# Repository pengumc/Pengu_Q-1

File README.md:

Pengu_Q-1
=========

Q1 quadruped robot control software

usage:
------
 - build the quadruped library under /quadruped
 - run qpview.py from within /hmatrix_visualizer (you may need to help your os with finding the quadruped library)

media:
------
www.youtube.com/watch?v=90h8AxxW2I0

http://pengurobotics.com/projects/Q1

http://hackaday.io/project/3229-pengu-q1-quadruped

3D printer files
----------------
http://www.thingiverse.com/thing:161885

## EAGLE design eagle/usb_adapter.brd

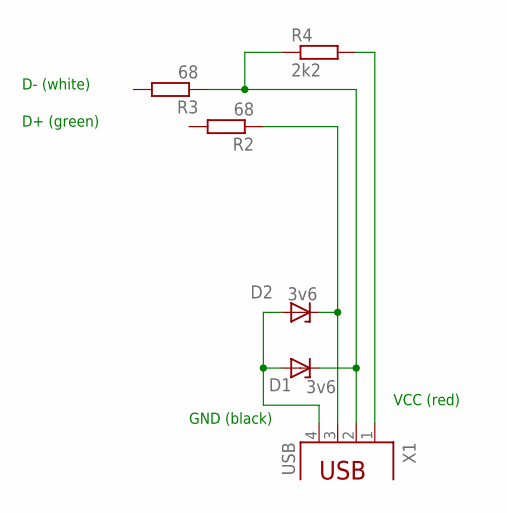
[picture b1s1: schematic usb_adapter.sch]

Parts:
D1, D2: 3v6; DO34Z7
R2, R3: 68; 0204/7
R4: 2k2; 0204/7
X1: USB; PN61729

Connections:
DMIN: D1.C, R3.1, R4.1, X1.2
DPLUS: D2.C, R2.1, X1.3
GND: D1.A, D2.A, X1.4
unnamed: R4.2, X1.1

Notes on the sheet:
D- (white)
D+ (green)
GND (black)
VCC (red)

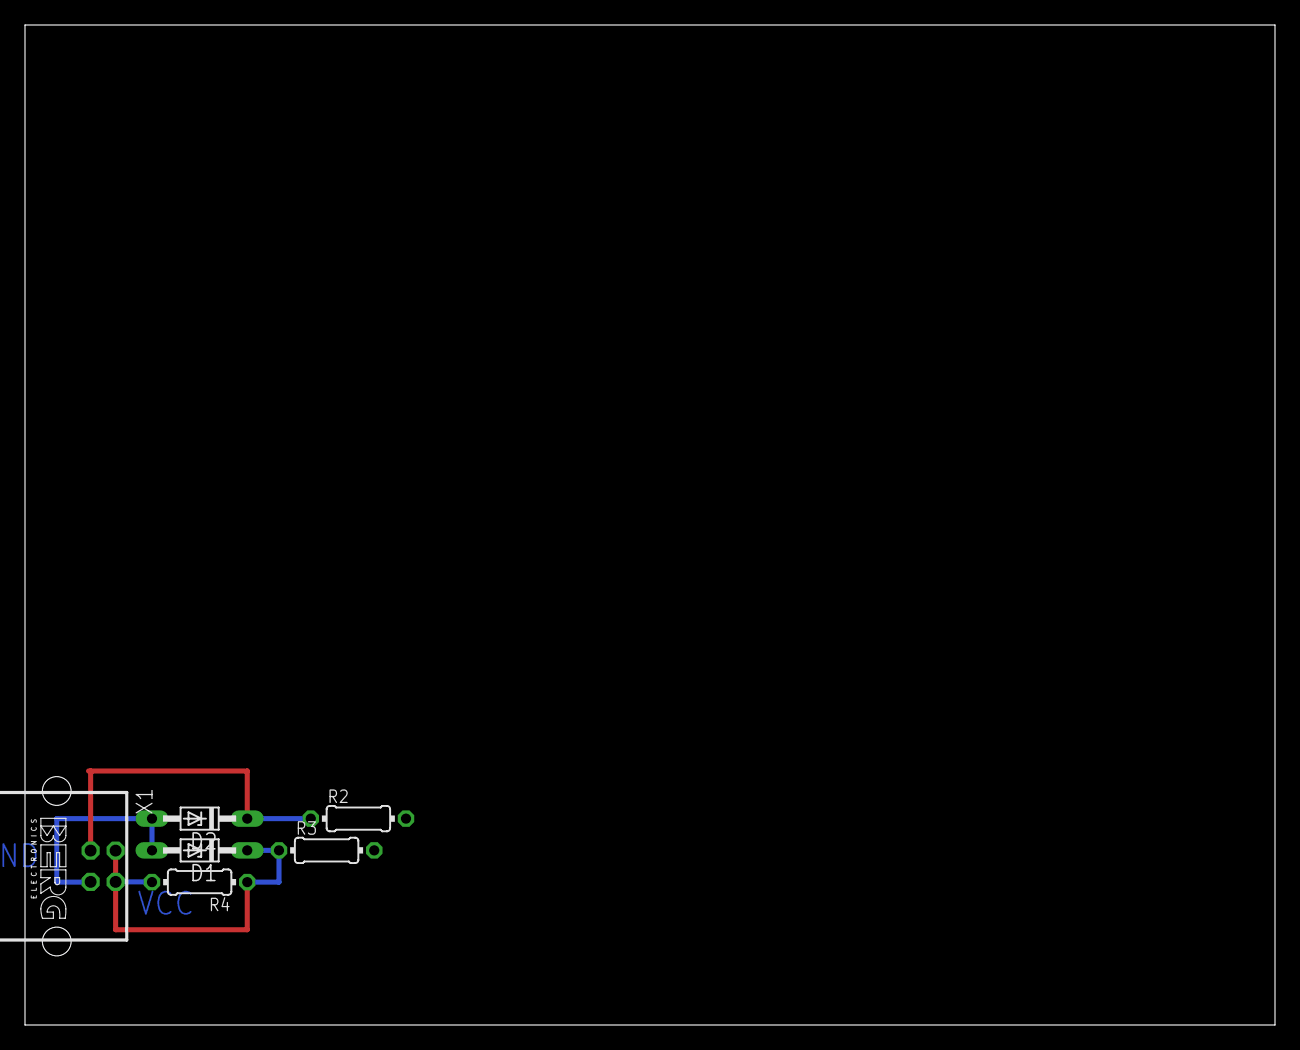
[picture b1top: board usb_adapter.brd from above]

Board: 2 copper layers, 100.0 x 80.0 mm, 6 parts (0 on the bottom side), 4 nets.

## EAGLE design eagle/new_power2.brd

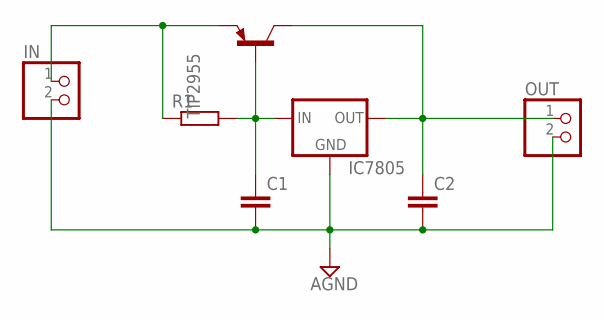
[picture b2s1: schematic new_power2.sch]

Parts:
C1, C2: C-EU025-024X044; C025-024X044
IC7805: 78XXL
IN: PINHD-1X2; 1X02
OUT: PINHD-1X2; 1X02
R1: R-EU_0204/5; 0204/5
TIP2955: -PNP-TO220; TO220

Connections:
AGND: C1.2, C2.2, IC7805.GND, IN.2, OUT.2
unnamed: IN.1, R1.1, TIP2955.3 (E)
unnamed: C1.1, IC7805.IN, R1.2, TIP2955.1 (B)
unnamed: C2.1, IC7805.OUT, OUT.1, TIP2955.2 (C)

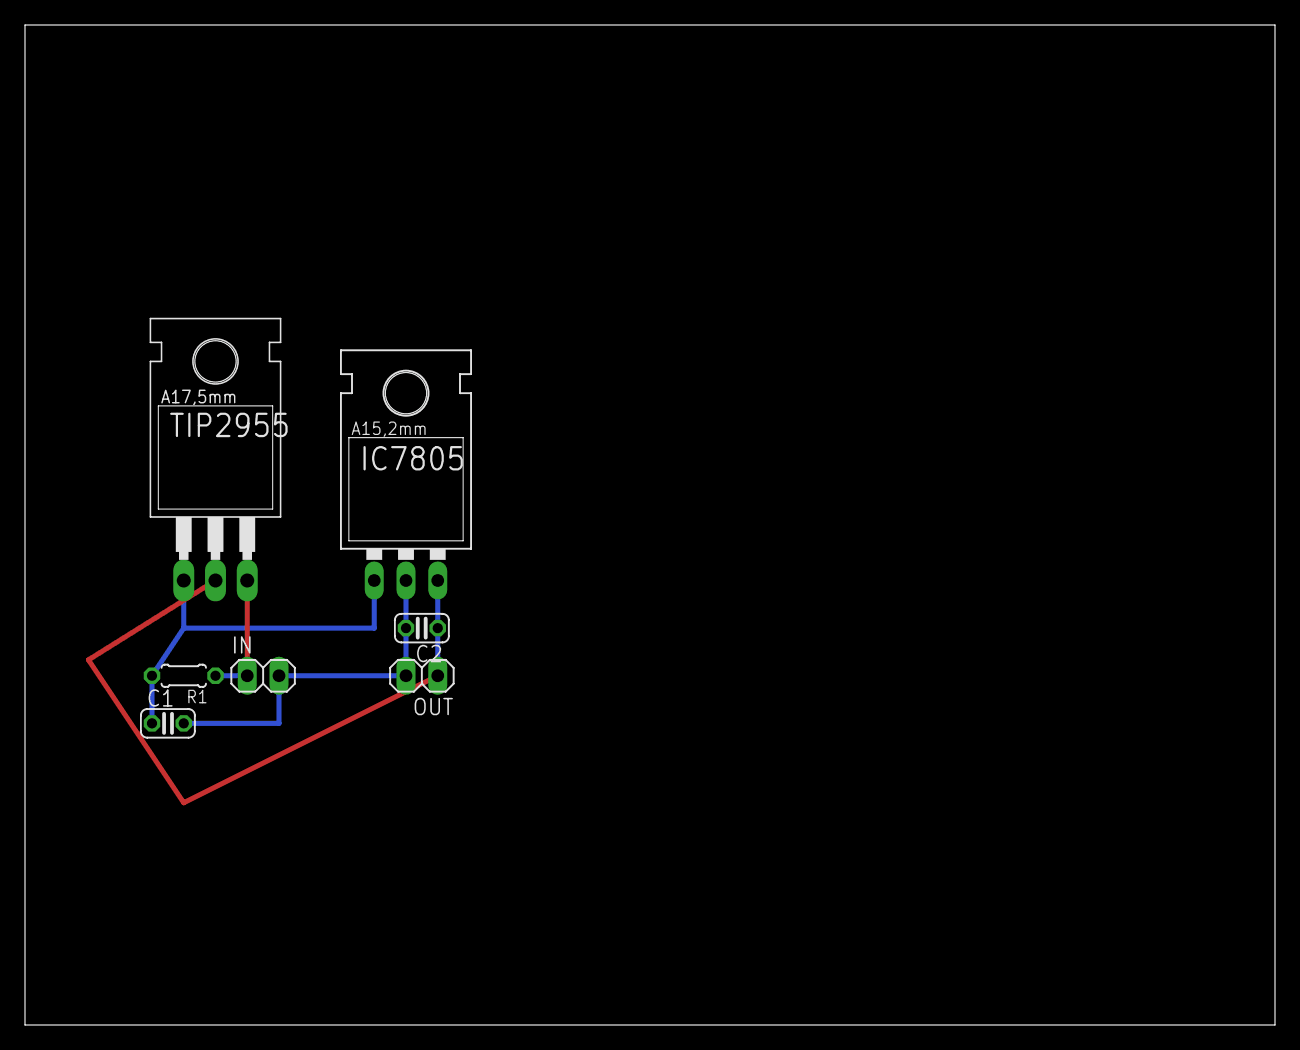
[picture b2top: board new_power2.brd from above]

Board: 2 copper layers, 100.0 x 80.0 mm, 7 parts (0 on the bottom side), 4 nets.

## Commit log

2013-11-02 start
2013-11-03 rudimentary screen
2013-11-16 messing around
2013-11-16 quit event
2013-12-31 add tested files
2013-12-31 added q1webgl files
2013-12-31 cleanup
    webgl enabled
2014-01-18 3d position sync, hover+az
2014-01-18 a/z for legs and body
2014-03-21 more classes
2014-03-21 visualization mockup
2014-03-22 unfinished pivot
2014-03-24 code fixes, added linux support
2014-03-24 added utility, fixed makefile for linux
2014-03-24 pivot done
2014-03-24 doc update
2014-03-27 stash
2014-04-26 HMatrix exposed
2014-05-08 python version of getch
2014-05-08 style fix
2014-05-08 simple start
2014-05-08 new HMatrix constructor
2014-05-08 wrapper groundwork done
2014-05-08 trying for an updating pyplot
2014-05-08 SelfDot
2014-05-08 doc update + threaded plot
2014-05-08 configure pivot orientation
2014-05-09 linux threaded ctypes workaround
2014-05-09 transform tree
2014-05-09 hardcoded config
2014-05-09 xml based config
2014-05-12 added offset to pivot, axis_ is removed in favor of config by R
2014-05-12 change angle
2014-05-12 better doc update
2014-05-12 no pdfs
2014-05-12 start IK dev
2014-05-12 math
2014-05-13 succes with a single pivot
2014-05-13 2 pivot test
2014-05-13 IK testing
2014-05-13 3 pivots hardcoded with view
2014-05-14 IK working
2014-05-14 more doc
2014-05-26 start usbcom dev with hidapi
    libraries in bin are for 64 bit linux and windows (32 and 64 bit)
2014-05-26 fixes for makefile, minor other changes
2014-05-28 sync functions
2014-05-28 up down testing
2014-07-26 schematic fix + usb adapter
2014-07-27 CoM compiles, time for testing
2014-07-27 CoM bugfix, wrapper
2014-08-03 COM added + recalibrate
2014-08-03 documentation update
2014-08-03 first steps
2014-08-09 calibration bios
2014-08-10 at least it compiles now
2014-08-10 exposed gaitgenerator configuration
2014-08-11 added gaitgenerator velocity, fixed HL
2014-08-22 removed doc from repo
2014-08-22 config fix
2014-08-22 testing...
2014-08-24 added gaitgenerator step
2014-08-24 animated plots!
2014-08-24 topdown view
2014-08-25 gaitgenerator working
2014-09-12 added L_min in gaitgenerator
2014-09-12 moving towards support for new servocontroller
2014-09-13 broken. WriteServoPulsewidths works
2014-09-13 still broken, read works
2014-09-13 new servocontroller works
2014-09-14 meaning of offset changed. recalibrated
2014-09-19 config update, circle motion
2014-09-19 new class SpringGG
2014-09-19 forces are correct
2014-09-20 pattern check
2014-09-20 removed rogg gaitgenerator
2014-09-20 quadruped.cpp formatting
2014-09-20 basic functionality is there
2014-09-20 working demo
2014-09-21 quick mashup of temporary power board
2014-10-11 added equalize feet levels function
2014-10-11 updated makefile
2014-10-11 body rotation
2014-10-26 added controller support, renamed rotation functions
2014-10-26 inverse kinematics demo stuff
2014-11-04 simple body circle
2014-12-11 removed cpplint from github
2014-12-16 diagonal vector finding
2014-12-21 move to support pattern
2014-12-22 temporary rest vector
2014-12-22 stylecheck
2014-12-22 readme update
2014-12-22 working turning
2014-12-23 youtube turning demo
2014-12-27 added k to turn 0
2015-01-07 omnidirectional first working version
2015-01-10 moved plotting and library to their own thread
2015-01-10 terminal improvements and linux library thread fix
2015-01-10 show plot on 'p'
2015-01-11 walk testing
2015-01-13 rotation keybindings
2015-01-13 main.py is obsolete now
2015-01-16 moved imports
2015-01-19 added move_to_lift
2015-01-19 reconfigure
2015-02-01 kicad stuff
2015-02-01 current sensor
